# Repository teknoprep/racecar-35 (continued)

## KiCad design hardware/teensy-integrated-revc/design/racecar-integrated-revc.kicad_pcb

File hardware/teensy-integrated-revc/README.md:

# Rev C — actual electrical engineering prototype

**The requested Gerbers and separate PTH/NPTH drills now exist.** These are not
pads exported from the former rendering: the board has **136 PCB parts, 76 nets,
routed copper and matching native schematic**.

## Deliverables

- **`Racecar-RevC-GERBERS-ENGINEERING-PROTOTYPE.zip`** — 9 Gerber layers, separate
  plated/non-plated drills and maps, schematic PDF, selected BOM, assembly extras,
  placement CSV, fabrication/assembly/bring-up notes, editable KiCad sources,
  validation reports, assembled preview and SHA256 manifest.
- **`REV-C-ASSEMBLED-ENGINEERING-PROTOTYPE.png`** — view of this actual routed PCB.
  Module/part bodies are illustrative, not mechanical fit certificates.
- `design/` — authoritative electrical CAD and manufacturing documents.
- `electrical/` — generation, routing, finishing, verification and rendering scripts.

**Status: UNBUILT ENGINEERING PROTOTYPE, not independently approved or physically
validated.** Full ERC and DRC report zero violations and zero unconnected items;
392 connected pads match the schematic; 427 pin/geometry/calculation assertions pass.
These do NOT establish 5 A thermal capability, RF performance, component authenticity,
automotive qualification or a fully working firmware product.

## Important differences from the earlier concept

- Left terminal bank: **J3 TACH / J4 OIL / J5 NTC / J6 AEM / J1 POWER / J2 SCREEN**.
  Names and exact pin order are in `design/ASSEMBLY.md`; they agree with the netlist.
- Separate AUX and NET **TRACO TSR 1-2433** regulators run from Pololu protected
  input (VRP), not from marginal 5 V or the Teensy's 3V3 output.
- C1 polarized input bulk is **after reverse-polarity protection** on VRP.
- Oil/AEM/NTC inputs have independent clamps, RC filtering and TMUX1511 isolation.
  **Oil gain is 0.500; coolant uses 4.096 V / 2.49k excitation and 0.500 sensing.**
  Existing firmware still needs matching oil/coolant conversions and sender calibration.
- WiFi is the internal-antenna WROOM-1-N8R2, with buffered SPI and protected reset/
  service interfaces. The new coprocessor software/upload transport is NOT implemented.
- CR2032 feeds Teensy VBAT through **J9 and a short removable auxiliary-pad lead**.
  The outer-row sockets do not carry VBAT. Fresh-time/validity firmware work remains.
- MPU-6050 is selected to match the existing driver, but genuine authorized stock
  is a procurement/lifecycle gate; do not substitute a different IMU without revision.

## Export and reproducibility

Re-export the current completed CAD, without regenerating/rerouting it:

```sh
/usr/bin/python3 hardware/teensy-integrated-revc/electrical/verify.py
/usr/bin/python3 hardware/teensy-integrated-revc/fabrication/export.py --engineering-prototype
```

That explicit mode makes no human-approval claim. It still requires all documents,
real nets/tracks, pin contracts, clean full-severity ERC/DRC, no unconnected items,
exact connected-pad equality, matching render identity, all manufacturing layers,
separate drills and ZIP/hash verification. Default mode instead requires a real,
named, hash-pinned independent review. **Never fabricate an approval record.**

**Do not casually run `electrical/generate.py`: it overwrites the routed PCB.**
The reproducible development sequence is generator → schematic → route.py (locked
power/RF + DSN) → Freerouting 1.9.0 (`-mp 50`) → route.py `--finish` →
complete_routes.py (documented final two connections) → finish_artwork.py → full
checks → render.py → export. The saved native PCB is the authoritative result;
a differently optimized router result requires reviewing the manual-finishing step.
KiCad 9.0.8/system Python pcbnew are used. Rendering uses downloaded KiCad WRL bodies
and the explicitly approximate original module models from the archived carrier.

The old `preview/`, `handoff/`, `REV-C-INTEGRATED-PREVIEW.png`, concept connection
SVG and design-review RFQ ZIP are retained as history, **not current fabrication
sources**. Their candidate/unfinished-circuit wording is superseded by `design/`.
The same applies to earlier requirements where they differ from these selected
circuits. A/B remain archived, not alternate integrated boards.

No firmware version bump, flash, OTA publication, purchase or fabrication order was
performed by this hardware export. Read `design/BRINGUP.md` before applying power.

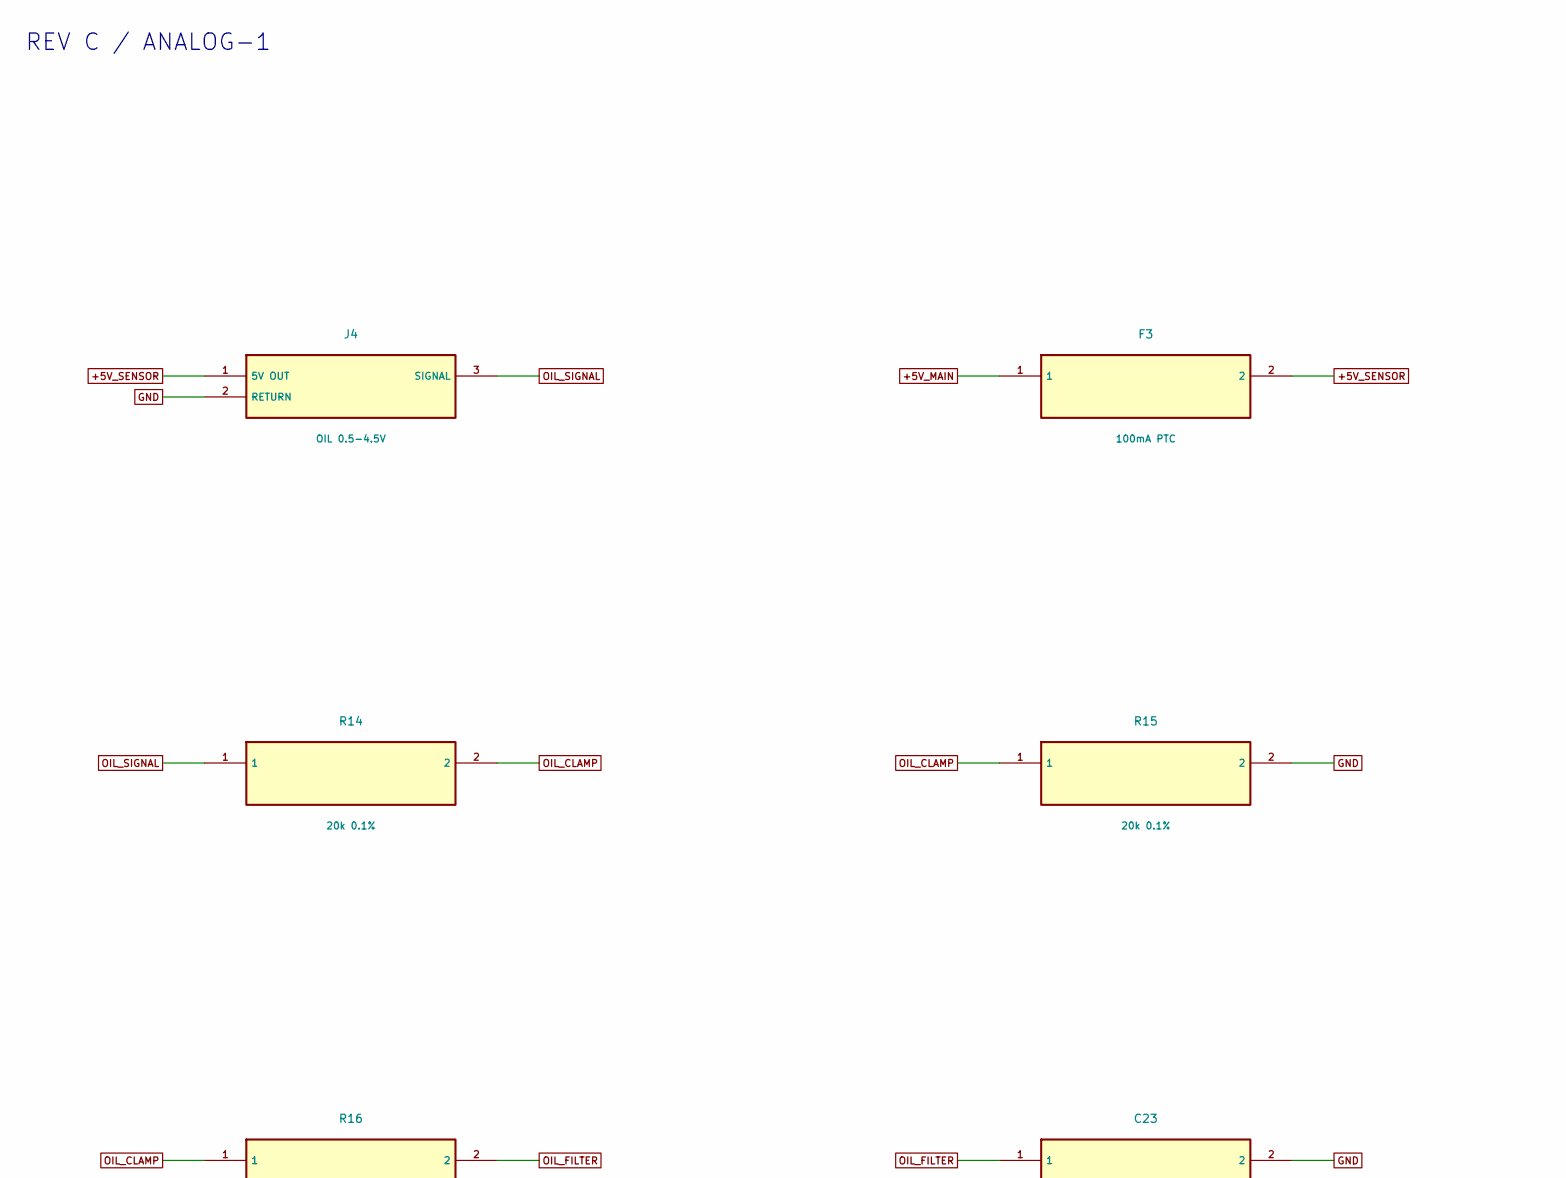
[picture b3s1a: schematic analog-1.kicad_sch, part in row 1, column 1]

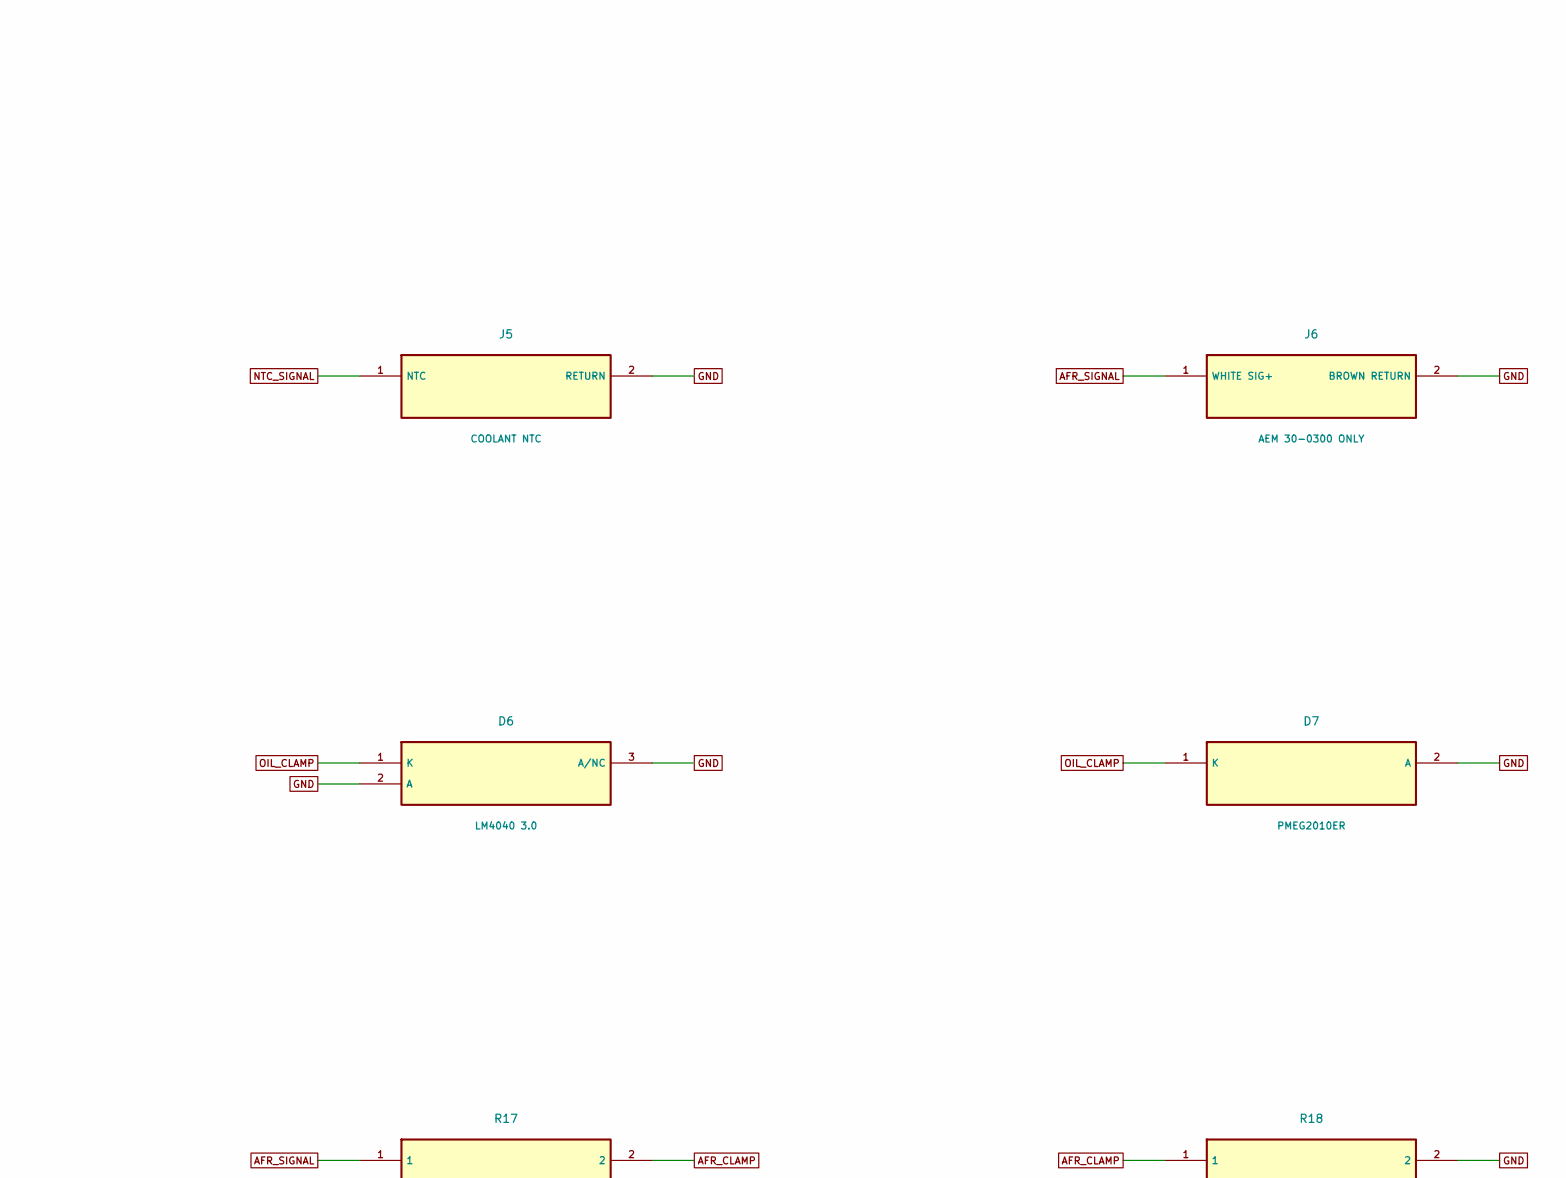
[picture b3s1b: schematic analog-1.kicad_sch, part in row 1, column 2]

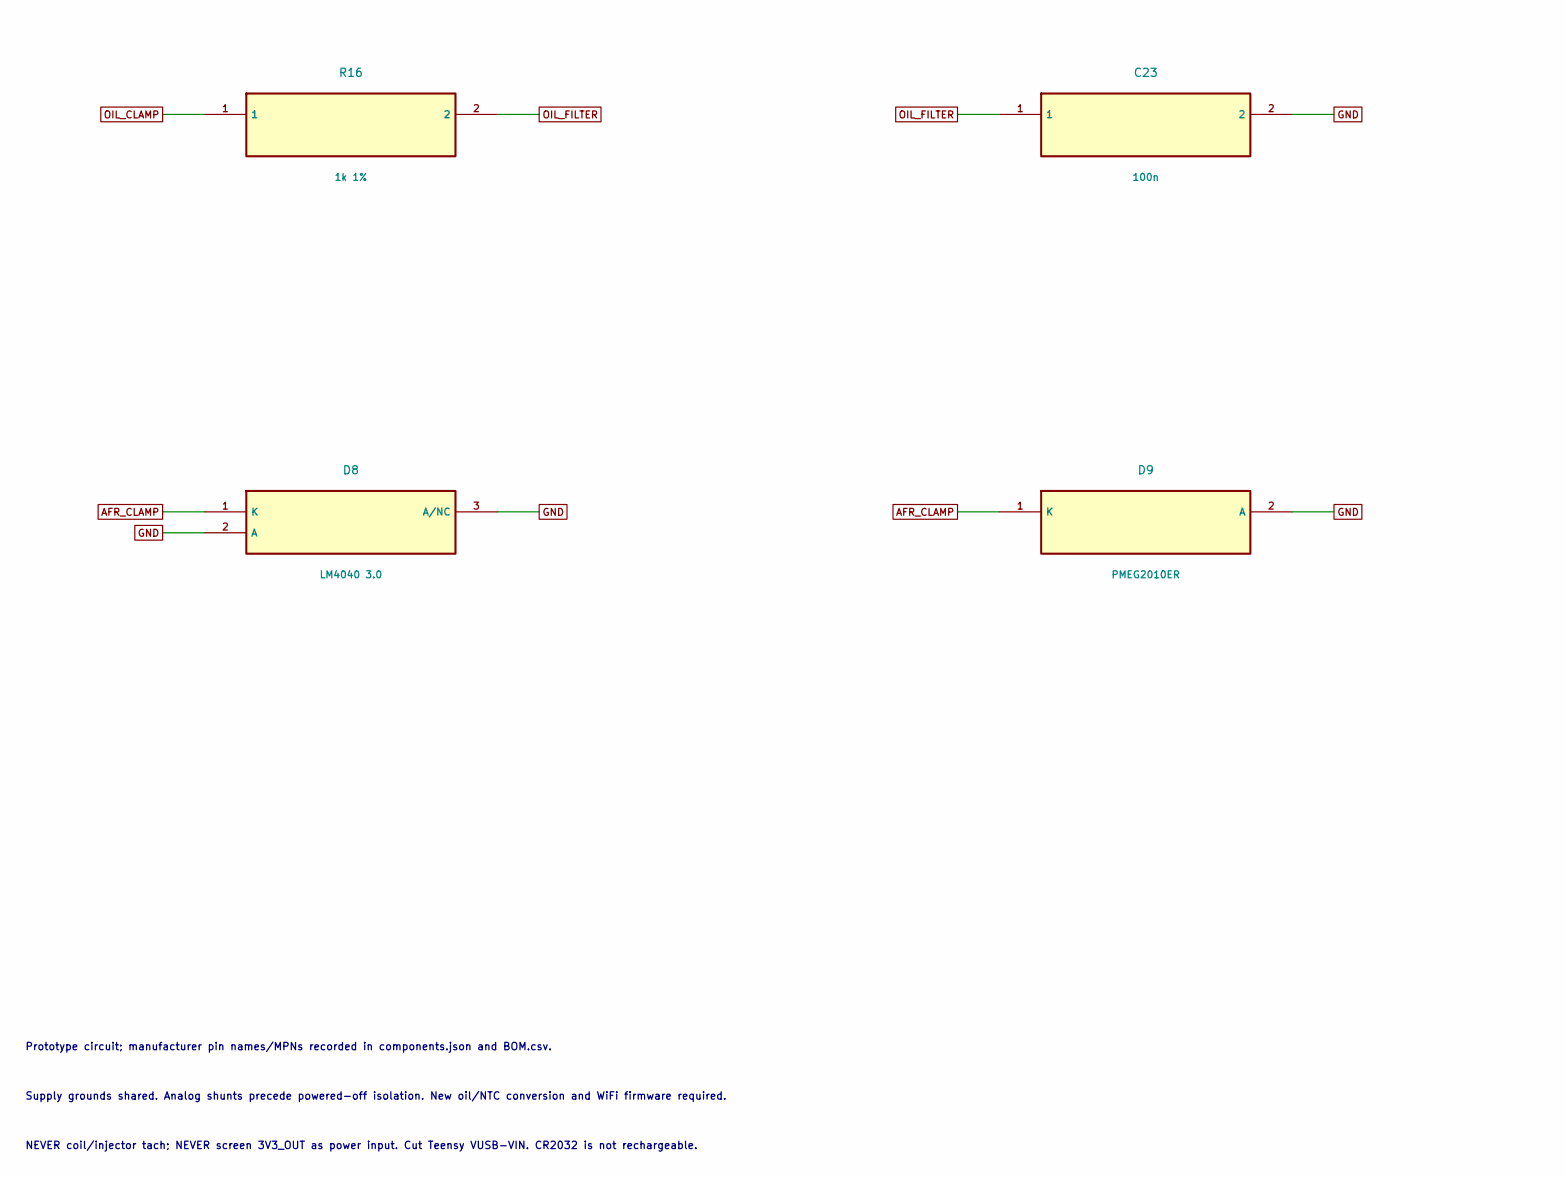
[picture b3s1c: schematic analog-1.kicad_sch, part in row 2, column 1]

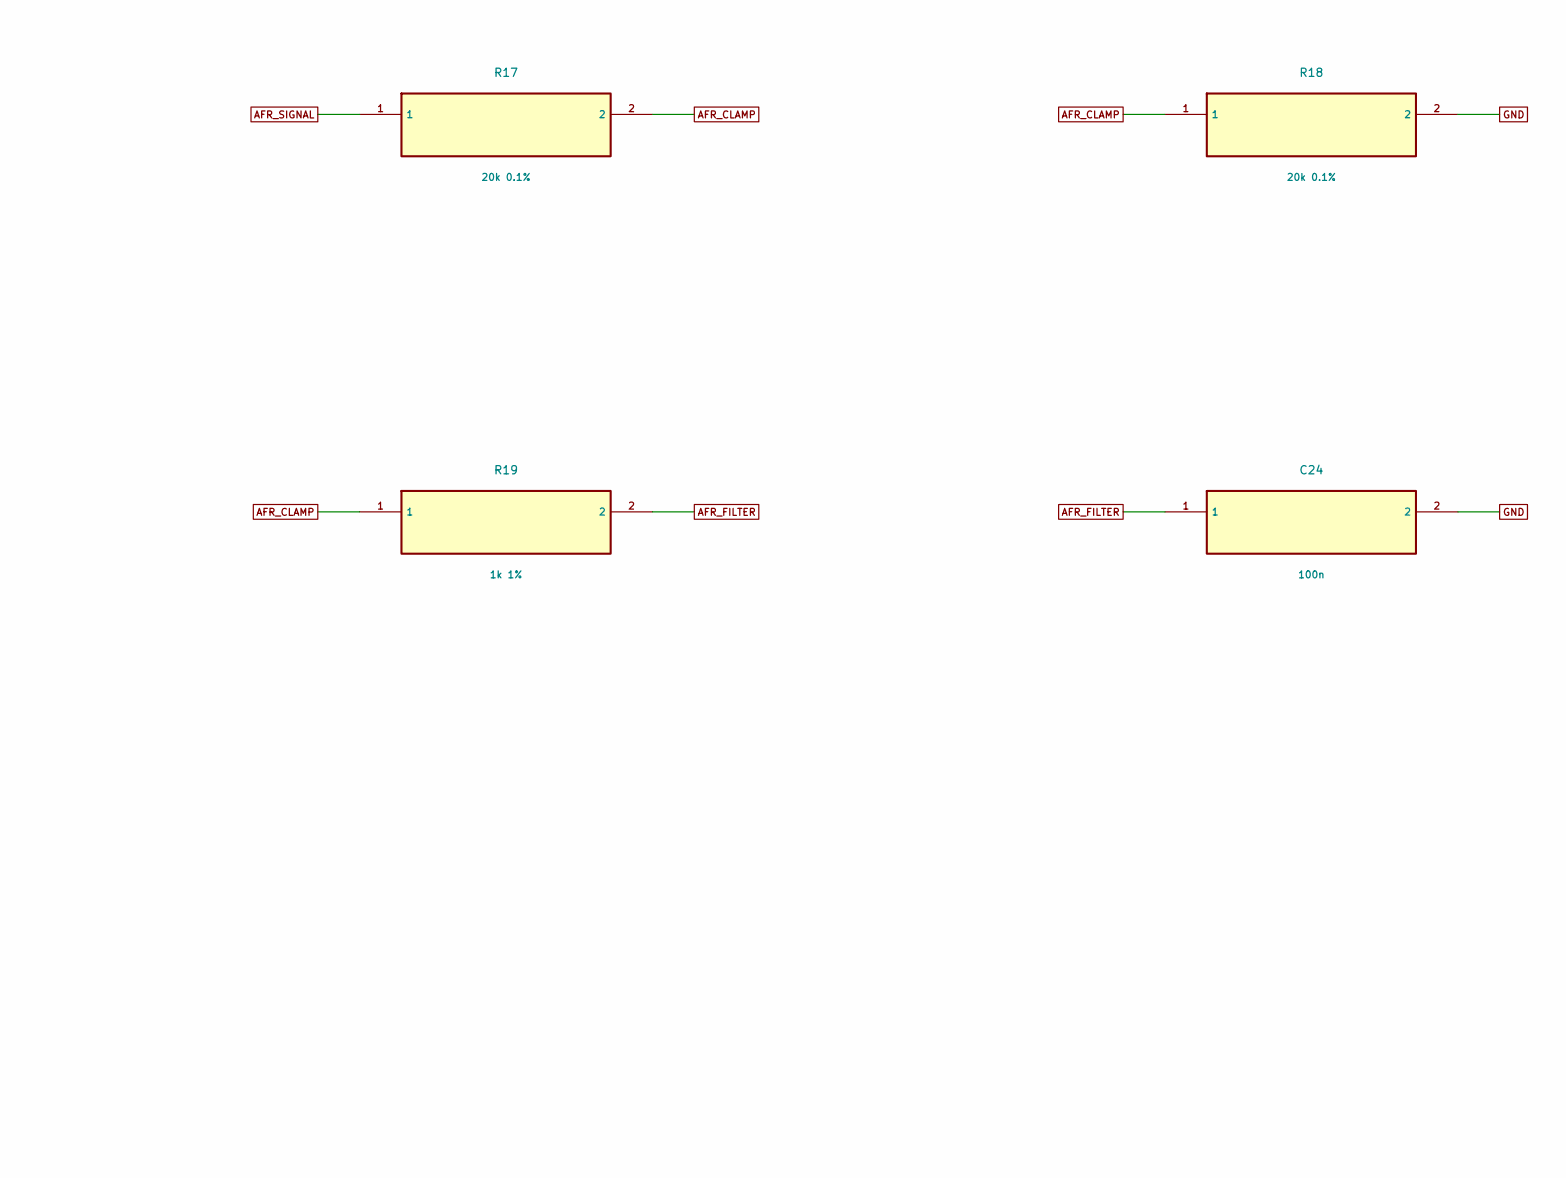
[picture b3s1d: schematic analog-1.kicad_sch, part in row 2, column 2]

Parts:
C23, C24: 100n; C_0805_2012Metric
D6, D8: LM4040 3.0; SOT-23
D7, D9: PMEG2010ER; Nexperia_CFP3_SOD-123W
F3: 100mA PTC; Fuse_1206_3216Metric
J4: OIL 0.5-4.5V; TerminalBlock_Phoenix_MKDS-1,5-3-5.08_1x03_P5.08mm_Horizont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
J5: COOLANT NTC; TerminalBlock_Phoenix_MKDS-1,5-2-5.08_1x02_P5.08mm_Horizont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
J6: AEM 30-0300 ONLY; TerminalBlock_Phoenix_MKDS-1,5-2-5.08_1x02_P5.08mm_Horizont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
R14, R15, R17, R18: 20k 0.1%; R_0805_2012Metric
R16, R19: 1k 1%; R_0805_2012Metric

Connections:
+5V_MAIN: F3.1; also elsewhere on the board
+5V_SENSOR: F3.2, J4.1 (5V OUT)
AFR_CLAMP: D8.1 (K), D9.1 (K), R17.2, R18.1, R19.1
AFR_FILTER: C24.1, R19.2; also elsewhere on the board
AFR_SIGNAL: J6.1 (WHITE SIG+), R17.1
GND: C23.2, C24.2, D6.2 (A), D6.3 (A/NC), D7.2 (A), D8.2 (A), D8.3 (A/NC), D9.2 (A), J4.2 (RETURN), J5.2 (RETURN), J6.2 (BROWN RETURN), R15.2, R18.2; also elsewhere on the board
NTC_SIGNAL: J5.1 (NTC); also elsewhere on the board
OIL_CLAMP: D6.1 (K), D7.1 (K), R14.2, R15.1, R16.1
OIL_FILTER: C23.1, R16.2; also elsewhere on the board
OIL_SIGNAL: J4.3 (SIGNAL), R14.1

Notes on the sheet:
REV C / ANALOG-1
Prototype circuit; manufacturer pin names/MPNs recorded in components.json and BOM.csv.
Supply grounds shared. Analog shunts precede powered-off isolation. New oil/NTC conversion and WiFi firmware required.
NEVER coil/injector tach; NEVER screen 3V3_OUT as power input. Cut Teensy VUSB-VIN. CR2032 is not rechargeable.

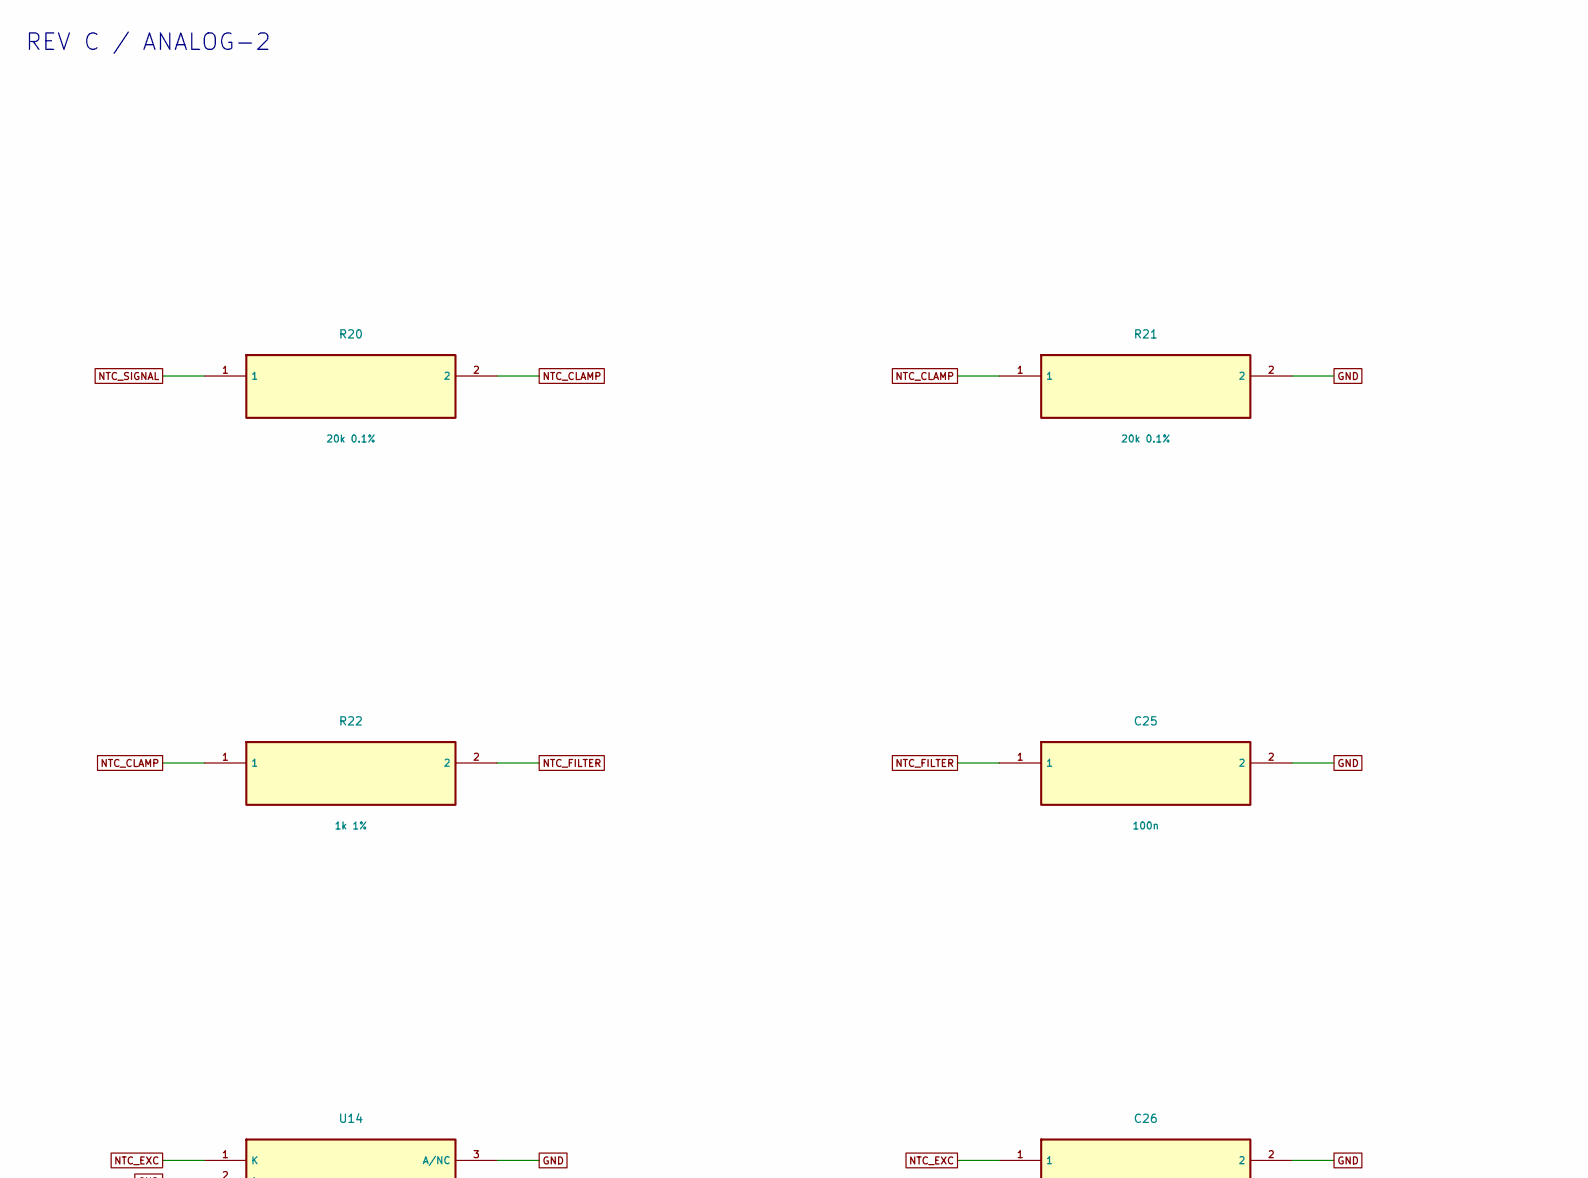
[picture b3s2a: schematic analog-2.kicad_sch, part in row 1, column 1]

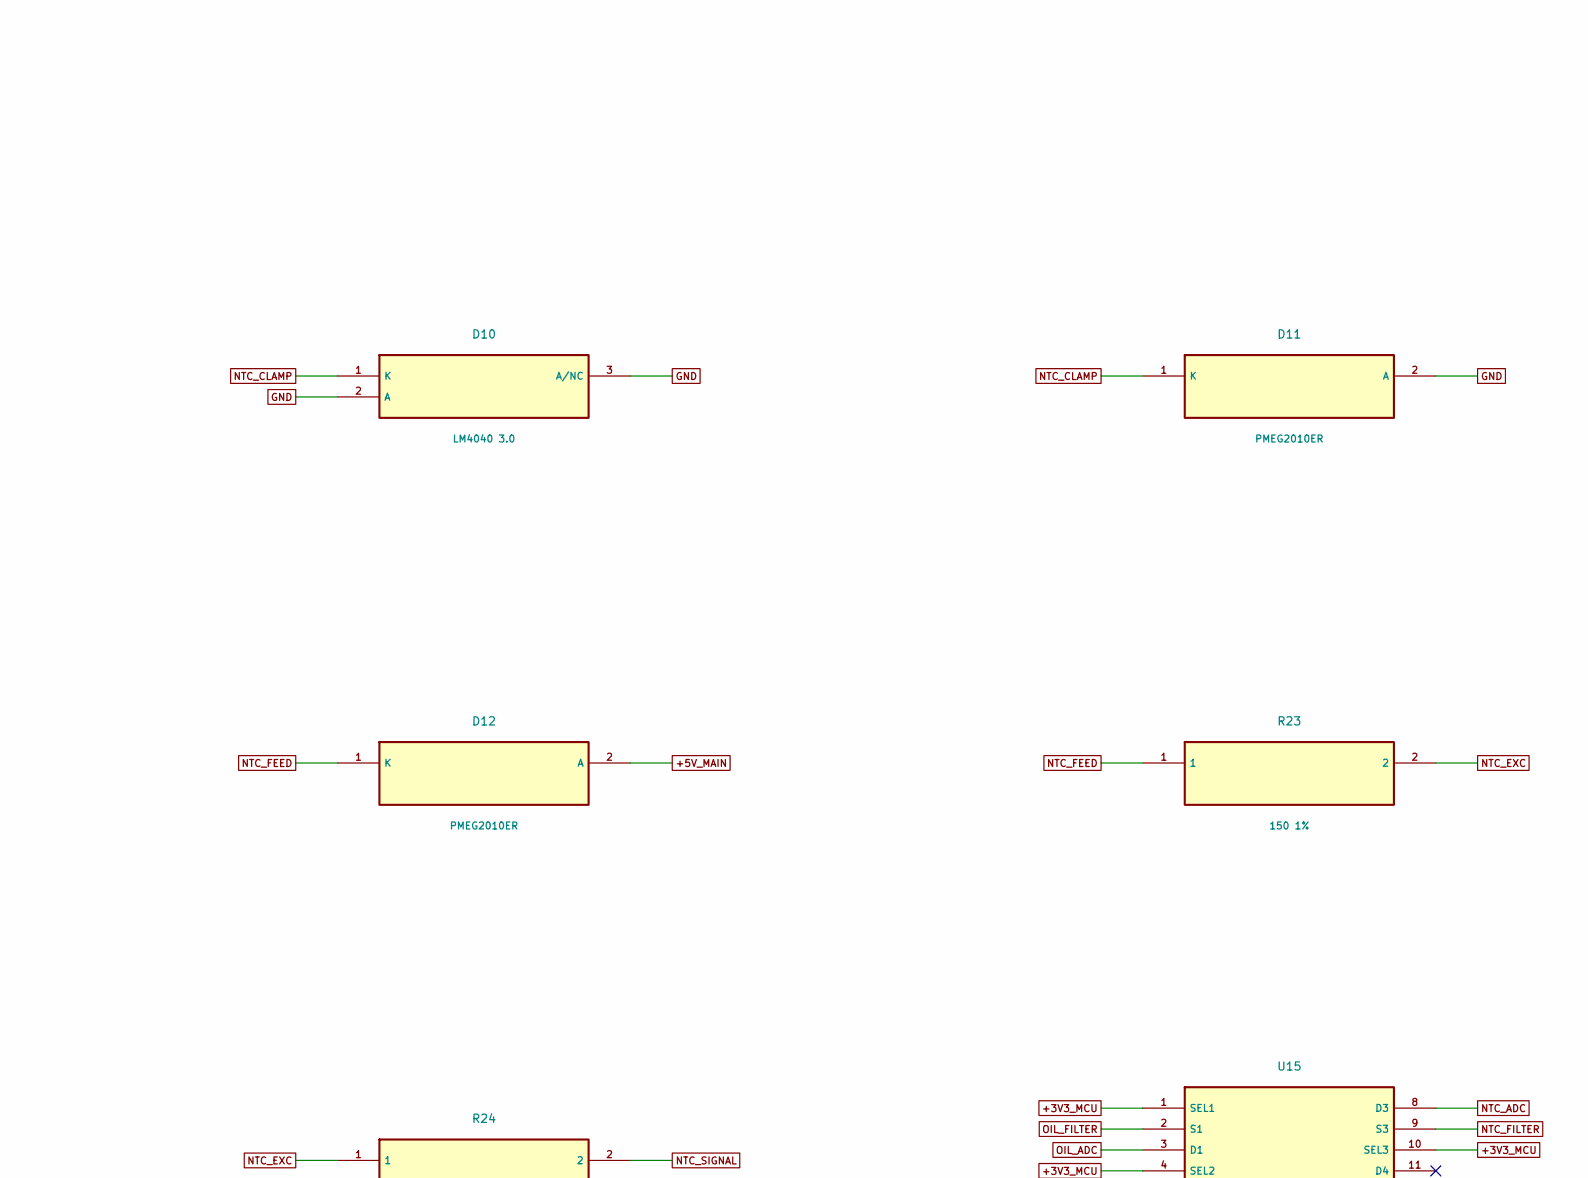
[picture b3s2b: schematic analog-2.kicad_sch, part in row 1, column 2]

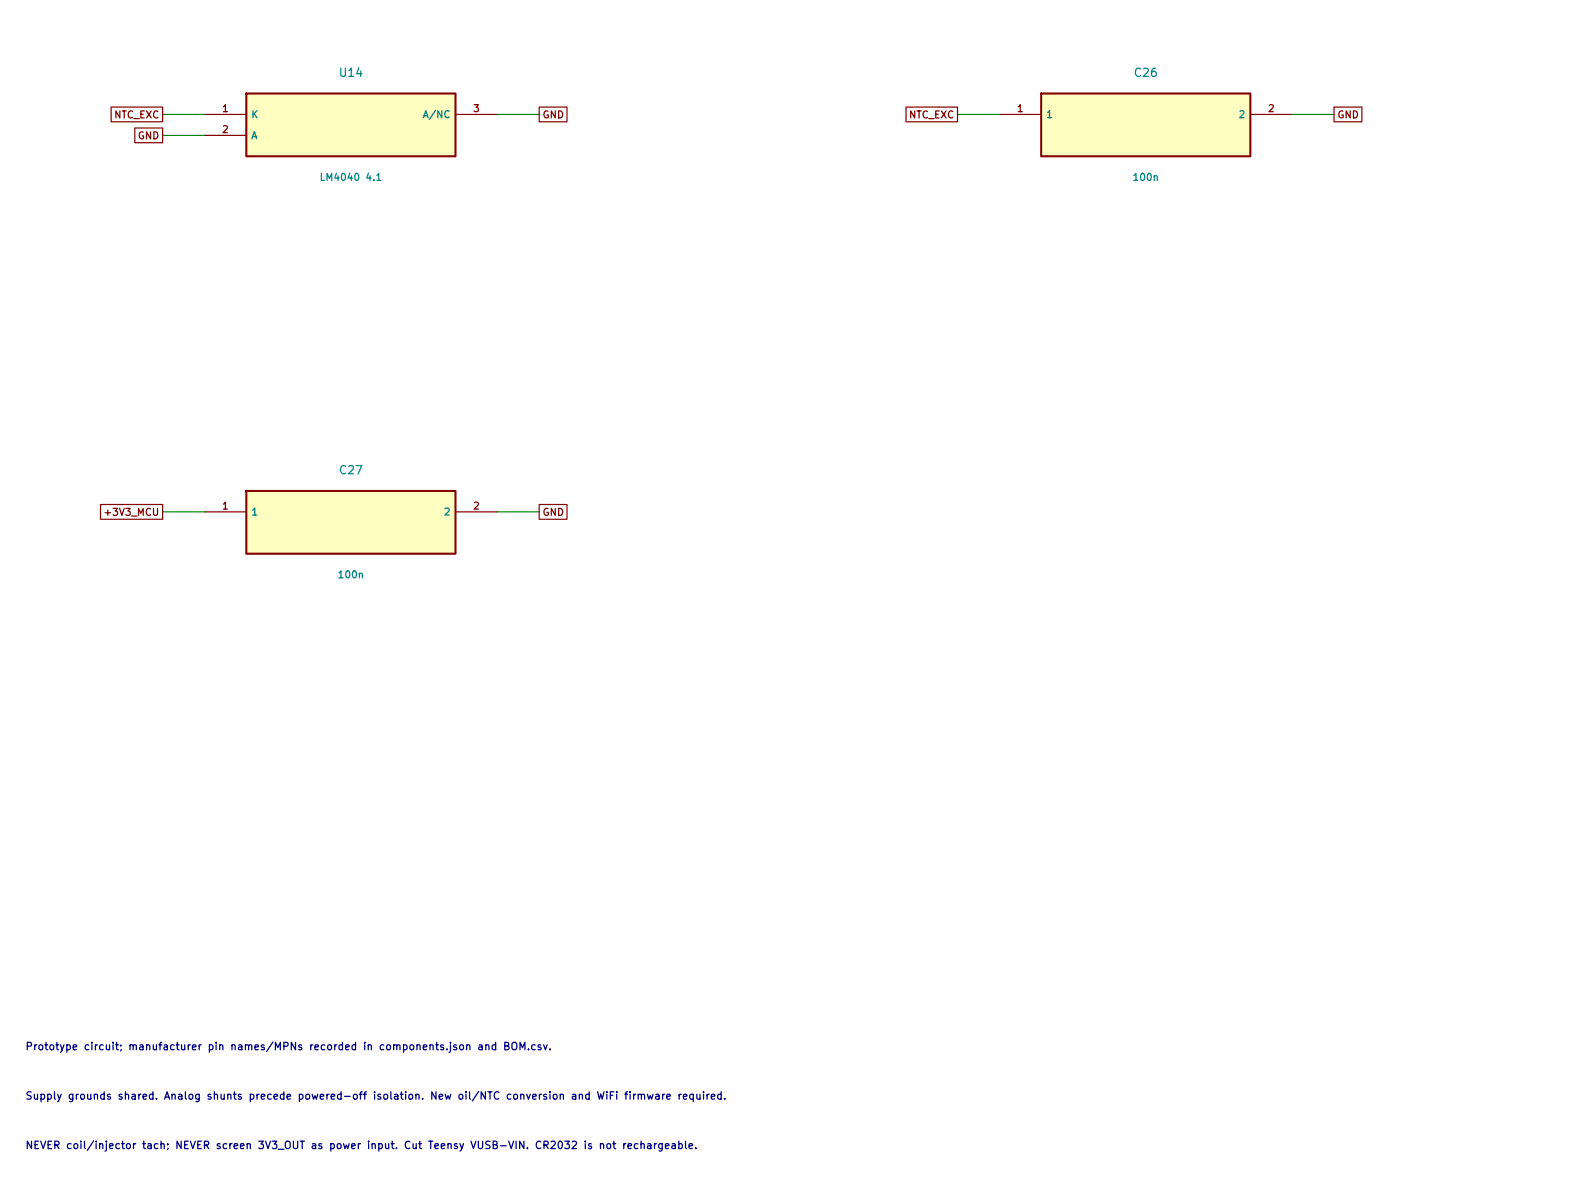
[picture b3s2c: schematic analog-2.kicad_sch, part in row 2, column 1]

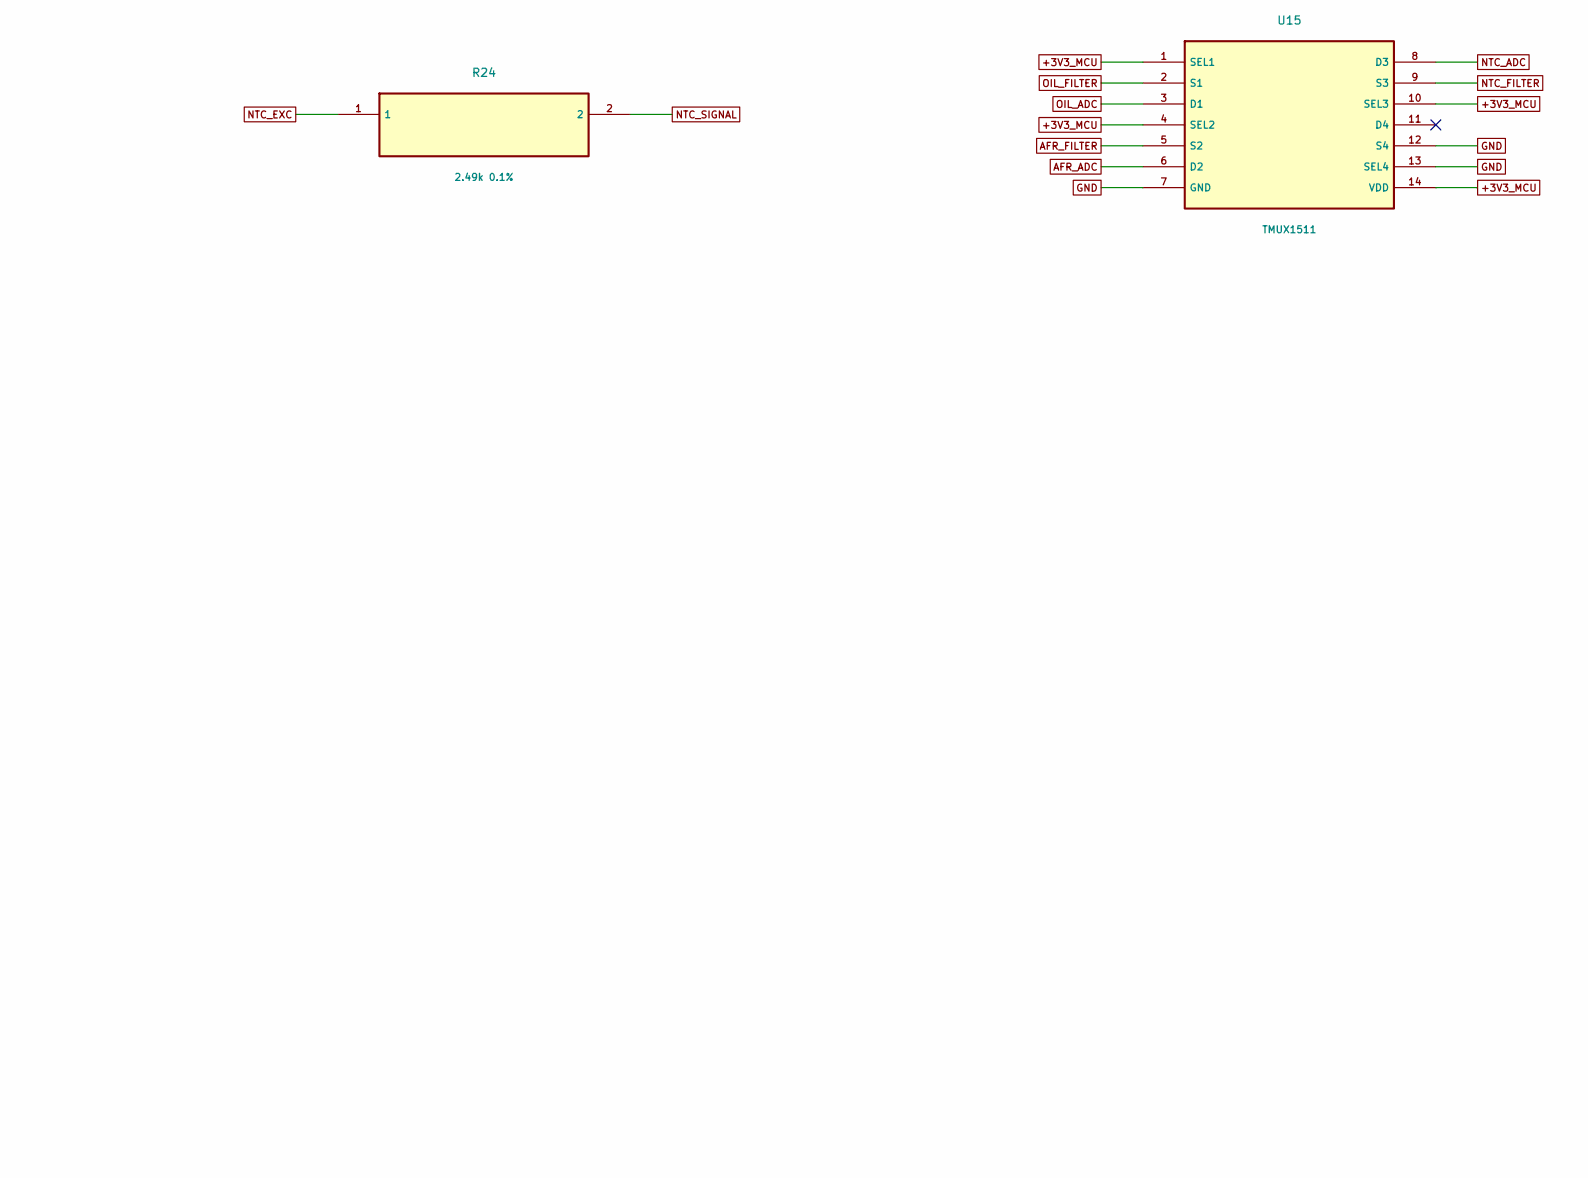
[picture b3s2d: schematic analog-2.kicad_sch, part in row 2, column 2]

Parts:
C25, C26, C27: 100n; C_0805_2012Metric
D10: LM4040 3.0; SOT-23
D11, D12: PMEG2010ER; Nexperia_CFP3_SOD-123W
R20, R21: 20k 0.1%; R_0805_2012Metric
R22: 1k 1%; R_0805_2012Metric
R23: 150 1%; R_0805_2012Metric
R24: 2.49k 0.1%; R_0805_2012Metric
U14: LM4040 4.1; SOT-23
U15: TMUX1511; TSSOP-14_4.4x5mm_P0.65mm

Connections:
+3V3_MCU: C27.1, U15.1 (SEL1), U15.4 (SEL2), U15.10 (SEL3), U15.14 (VDD); also elsewhere on the board
+5V_MAIN: D12.2 (A); also elsewhere on the board
AFR_ADC: U15.6 (D2); also elsewhere on the board
AFR_FILTER: U15.5 (S2); also elsewhere on the board
GND: C25.2, C26.2, C27.2, D10.2 (A), D10.3 (A/NC), D11.2 (A), R21.2, U14.2 (A), U14.3 (A/NC), U15.7 (GND), U15.12 (S4), U15.13 (SEL4); also elsewhere on the board
NTC_ADC: U15.8 (D3); also elsewhere on the board
NTC_CLAMP: D10.1 (K), D11.1 (K), R20.2, R21.1, R22.1
NTC_EXC: C26.1, R23.2, R24.1, U14.1 (K)
NTC_FEED: D12.1 (K), R23.1
NTC_FILTER: C25.1, R22.2, U15.9 (S3)
NTC_SIGNAL: R20.1, R24.2; also elsewhere on the board
OIL_ADC: U15.3 (D1); also elsewhere on the board
OIL_FILTER: U15.2 (S1); also elsewhere on the board

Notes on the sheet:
REV C / ANALOG-2
Prototype circuit; manufacturer pin names/MPNs recorded in components.json and BOM.csv.
Supply grounds shared. Analog shunts precede powered-off isolation. New oil/NTC conversion and WiFi firmware required.
NEVER coil/injector tach; NEVER screen 3V3_OUT as power input. Cut Teensy VUSB-VIN. CR2032 is not rechargeable.

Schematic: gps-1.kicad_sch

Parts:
C13, C16, C17, C18: 100n; C_0805_2012Metric
C14: 10u; C_0805_2012Metric
C15: 100pF C0G; C_0402_1005Metric
D3: RF ESD; D_SOD-882
J8: GPS SMA FEMALE; SMA_Amphenol_901-143_Horizontal
L1: 27nH RF choke; L_0402_1005Metric
R3: 10R 1%; R_0805_2012Metric
U8: NEO-M9N-00B; ublox_NEO
U9: TPS2553; SOT-23-6
U10: SN74LVC1G125; SOT-23-5

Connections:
+3V3_AUX: C13.1, C14.1, C16.1, C18.1, U8.2 (D_SEL), U8.22 (V_BCKP), U8.23 (VCC), U9.1 (IN), U9.3 (EN), U9.5 (ILIM), U10.5 (VCC); also elsewhere on the board
ANT_BIAS: C17.1, L1.2, R3.2
ANT_SWITCH: R3.1, U9.6 (OUT)
GND: C13.2, C14.2, C16.2, C17.2, C18.2, D3.2, J8.2, U8.4 (EXTINT), U8.7 (V_USB), U8.10 (GND), U8.12 (GND), U8.13 (GND), U8.24 (GND), U9.2 (GND), U10.1 (OE_N), U10.3 (GND); also elsewhere on the board
GPS_RX_AUX: U8.21 (RXD), U10.4 (Y)
GPS_TX_AUX: U8.20 (TXD); also elsewhere on the board
GPS_TX_MCU: U10.2 (A); also elsewhere on the board
RF_ANT: C15.1, D3.1, J8.1, L1.1
RF_GNSS: C15.2, U8.11 (RF_IN)

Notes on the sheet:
REV C / GPS-1
Prototype circuit; manufacturer pin names/MPNs recorded in components.json and BOM.csv.
Supply grounds shared. Analog shunts precede powered-off isolation. New oil/NTC conversion and WiFi firmware required.
NEVER coil/injector tach; NEVER screen 3V3_OUT as power input. Cut Teensy VUSB-VIN. CR2032 is not rechargeable.

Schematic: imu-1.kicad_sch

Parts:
C9, C11: 100n; C_0805_2012Metric
C10: 10n; C_0805_2012Metric
C12: 2.2n; C_0805_2012Metric
R1, R2: 4.7k 1%; R_0805_2012Metric
U7: MPU-6050; InvenSense_QFN-24_4x4mm_P0.5mm

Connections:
+3V3_MCU: C9.1, C10.1, R1.1, R2.1, U7.8 (VLOGIC), U7.13 (VDD); also elsewhere on the board
GND: C9.2, C10.2, C11.2, C12.2, U7.1 (CLKIN), U7.9 (AD0), U7.11 (FSYNC), U7.18 (GND); also elsewhere on the board
IMU_CPOUT: C12.1, U7.20 (CPOUT)
IMU_REGOUT: C11.1, U7.10 (REGOUT)
IMU_SCL: R2.2, U7.23 (SCL); also elsewhere on the board
IMU_SDA: R1.2, U7.24 (SDA); also elsewhere on the board

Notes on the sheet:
REV C / IMU-1
Prototype circuit; manufacturer pin names/MPNs recorded in components.json and BOM.csv.
Supply grounds shared. Analog shunts precede powered-off isolation. New oil/NTC conversion and WiFi firmware required.
NEVER coil/injector tach; NEVER screen 3V3_OUT as power input. Cut Teensy VUSB-VIN. CR2032 is not rechargeable.

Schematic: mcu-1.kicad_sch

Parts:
BT1: CR2032 HOLDER; BatteryHolder_Keystone_1058_1x2032
C7, C8: 100n; C_0805_2012Metric
J7: CAN MODULE LOGIC; JST_XH_B4B-XH-A_1x04_P2.50mm_Vertical
J9: TO TEENSY VBAT/GND; JST_XH_B2B-XH-A_1x02_P2.50mm_Vertical

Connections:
+3V3_MCU: C7.1, C8.1, J7.1; also elsewhere on the board
CAN_RX: J7.4; also elsewhere on the board
CAN_TX: J7.3; also elsewhere on the board
GND: BT1.2 (CELL-), C7.2, C8.2, J7.2, J9.2; also elsewhere on the board
VBAT_CELL: BT1.1 (CELL+), J9.1

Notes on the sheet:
REV C / MCU-1
Prototype circuit; manufacturer pin names/MPNs recorded in components.json and BOM.csv.
Supply grounds shared. Analog shunts precede powered-off isolation. New oil/NTC conversion and WiFi firmware required.
NEVER coil/injector tach; NEVER screen 3V3_OUT as power input. Cut Teensy VUSB-VIN. CR2032 is not rechargeable.

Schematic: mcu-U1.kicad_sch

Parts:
U1: Teensy 4.1 SOCKETED; Teensy41_Socket

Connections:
+3V3_MCU: U1.15 (+3V3_MCU), U1.27 (+3V3_MCU); also elsewhere on the board
AFR_ADC: U1.31 (P20); also elsewhere on the board
CAN_RX: U1.28 (P23); also elsewhere on the board
CAN_TX: U1.29 (P22); also elsewhere on the board
DASH_RX_MCU: U1.36 (P15); also elsewhere on the board
DASH_TX_MCU: U1.37 (P14); also elsewhere on the board
GND: U1.1 (GND), U1.26 (GND), U1.39 (GND); also elsewhere on the board
GPS_RX_MCU: U1.9 (P7); also elsewhere on the board
GPS_TX_MCU: U1.10 (P8); also elsewhere on the board
IMU_SCL: U1.32 (P19); also elsewhere on the board
IMU_SDA: U1.33 (P18); also elsewhere on the board
NET_CS_MCU: U1.12 (P10); also elsewhere on the board
NET_IRQ_MCU: U1.7 (P5); also elsewhere on the board
NET_MISO_MCU: U1.14 (P12); also elsewhere on the board
NET_MOSI_MCU: U1.13 (P11); also elsewhere on the board
NET_RESET_ASSERT: U1.8 (P6); also elsewhere on the board
NET_SCK_MCU: U1.38 (P13); also elsewhere on the board
NTC_ADC: U1.34 (P17); also elsewhere on the board
OIL_ADC: U1.35 (P16); also elsewhere on the board
TACH_MCU: U1.11 (P9); also elsewhere on the board
TEENSY_VIN: U1.25 (TEENSY_VIN); also elsewhere on the board

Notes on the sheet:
REV C / MCU-U1
Prototype circuit; manufacturer pin names/MPNs recorded in components.json and BOM.csv.
Supply grounds shared. Analog shunts precede powered-off isolation. New oil/NTC conversion and WiFi firmware required.
NEVER coil/injector tach; NEVER screen 3V3_OUT as power input. Cut Teensy VUSB-VIN. CR2032 is not rechargeable.

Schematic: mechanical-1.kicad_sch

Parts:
H1, H2, H3, H4: M3 MOUNT; MountingHole_3.2mm_M3
TP1: GND; TestPoint_THTPad_D2.0mm_Drill1.0mm
TP2: +5V_MAIN; TestPoint_THTPad_D2.0mm_Drill1.0mm
TP3: +3V3_AUX; TestPoint_THTPad_D2.0mm_Drill1.0mm
TP4: +3V3_NET; TestPoint_THTPad_D2.0mm_Drill1.0mm
TP5: +3V3_MCU; TestPoint_THTPad_D2.0mm_Drill1.0mm

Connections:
+3V3_AUX: TP3.1; also elsewhere on the board
+3V3_MCU: TP5.1; also elsewhere on the board
+3V3_NET: TP4.1; also elsewhere on the board
+5V_MAIN: TP2.1; also elsewhere on the board
GND: TP1.1; also elsewhere on the board

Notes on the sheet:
REV C / MECHANICAL-1
Prototype circuit; manufacturer pin names/MPNs recorded in components.json and BOM.csv.
Supply grounds shared. Analog shunts precede powered-off isolation. New oil/NTC conversion and WiFi firmware required.
NEVER coil/injector tach; NEVER screen 3V3_OUT as power input. Cut Teensy VUSB-VIN. CR2032 is not rechargeable.

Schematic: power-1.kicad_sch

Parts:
C1: 100uF 50V; CP_Radial_D8.0mm_P3.50mm
C2: 470uF 10V; CP_Radial_D8.0mm_P3.50mm
C3, C5: 100n; C_0805_2012Metric
C4, C6: 10u; C_0805_2012Metric
D1: SMBJ20CA; D_SMB
D2: SS14; D_SMA
F1: 5A fuse; Fuse_Littelfuse-NANO2-451_453
F2: 4A fuse; Fuse_Littelfuse-NANO2-451_453
J1: POWER IN; TerminalBlock_Phoenix_MKDS-1,5-2-5.08_1x02_P5.08mm_Horizont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
JP1: MCU POWER; PinHeader_1x02_P2.54mm_Vertical
U2: Pololu D36V50F5; Pololu_D36V50F5
U3, U6: TSR 1-2433; Converter_DCDC_TRACO_TSR-1_THT

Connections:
+3V3_AUX: C4.1, U3.3 (VOUT); also elsewhere on the board
+3V3_NET: C6.1, U6.3 (VOUT); also elsewhere on the board
+5V_MAIN: D2.2 (A), F2.1, U2.1 (VOUT), U2.2 (VOUT); also elsewhere on the board
+5V_SCREEN: C2.1, F2.2; also elsewhere on the board
GND: C1.2, C2.2, C3.2, C4.2, C5.2, C6.2, D1.2, J1.2 (GND), U2.3 (GND), U2.4 (GND), U2.5 (GND), U2.6 (GND), U3.2 (GND), U6.2 (GND); also elsewhere on the board
TEENSY_VIN: JP1.2; also elsewhere on the board
VIN_DIODE: D2.1 (K), JP1.1
VIN_FUSED: D1.1, F1.2, U2.7 (VIN), U2.8 (VIN)
VIN_PROTECTED: C1.1, C3.1, C5.1, U2.9 (VRP), U2.10 (VRP), U3.1 (VIN), U6.1 (VIN)
VIN_RAW: F1.1, J1.1 (10-20V IN)

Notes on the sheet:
REV C / POWER-1
Prototype circuit; manufacturer pin names/MPNs recorded in components.json and BOM.csv.
Supply grounds shared. Analog shunts precede powered-off isolation. New oil/NTC conversion and WiFi firmware required.
NEVER coil/injector tach; NEVER screen 3V3_OUT as power input. Cut Teensy VUSB-VIN. CR2032 is not rechargeable.

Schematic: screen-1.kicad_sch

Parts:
C28, C29, C30, C31: 100n; C_0805_2012Metric
D13, D14: UART ESD; D_SOD-323
J2: SCREEN J10 ONLY; TerminalBlock_Phoenix_MKDS-1,5-4-5.08_1x04_P5.08mm_Horizont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
R25, R26: 100 1%; R_0805_2012Metric
R27, R28: 47k 1%; R_0805_2012Metric
U4, U5: SN74LVC1T45; SOT-23-6

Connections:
+3V3_MCU: C28.1, C30.1, R27.1, U4.1 (VCCA), U4.5 (DIR), U5.1 (VCCA); also elsewhere on the board
+5V_SCREEN: C29.1, C31.1, J2.2 (5V OUT), R28.1, U4.6 (VCCB), U5.6 (VCCB); also elsewhere on the board
DASH_RX_5V: R26.2, U5.4 (B)
DASH_RX_CABLE: D14.1, J2.3 (RX FROM), R26.1, R28.2
DASH_RX_MCU: U5.3 (A); also elsewhere on the board
DASH_TX_5V: R25.1, U4.4 (B)
DASH_TX_CABLE: D13.1, J2.4 (TX TO), R25.2
DASH_TX_MCU: R27.2, U4.3 (A); also elsewhere on the board
GND: C28.2, C29.2, C30.2, C31.2, D13.2, D14.2, J2.1 (GND), U4.2 (GND), U5.2 (GND), U5.5 (DIR); also elsewhere on the board

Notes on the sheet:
REV C / SCREEN-1
Prototype circuit; manufacturer pin names/MPNs recorded in components.json and BOM.csv.
Supply grounds shared. Analog shunts precede powered-off isolation. New oil/NTC conversion and WiFi firmware required.
NEVER coil/injector tach; NEVER screen 3V3_OUT as power input. Cut Teensy VUSB-VIN. CR2032 is not rechargeable.
